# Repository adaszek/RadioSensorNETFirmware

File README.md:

# RF24 config required

Changes in RF24Network_config.h:

```
#define DISABLE_USER_PAYLOADS
#define ENABLE_SLEEP_MODE
```

Changes in RF24Mech_config.h:
```
#define MESH_NOMASTER
```

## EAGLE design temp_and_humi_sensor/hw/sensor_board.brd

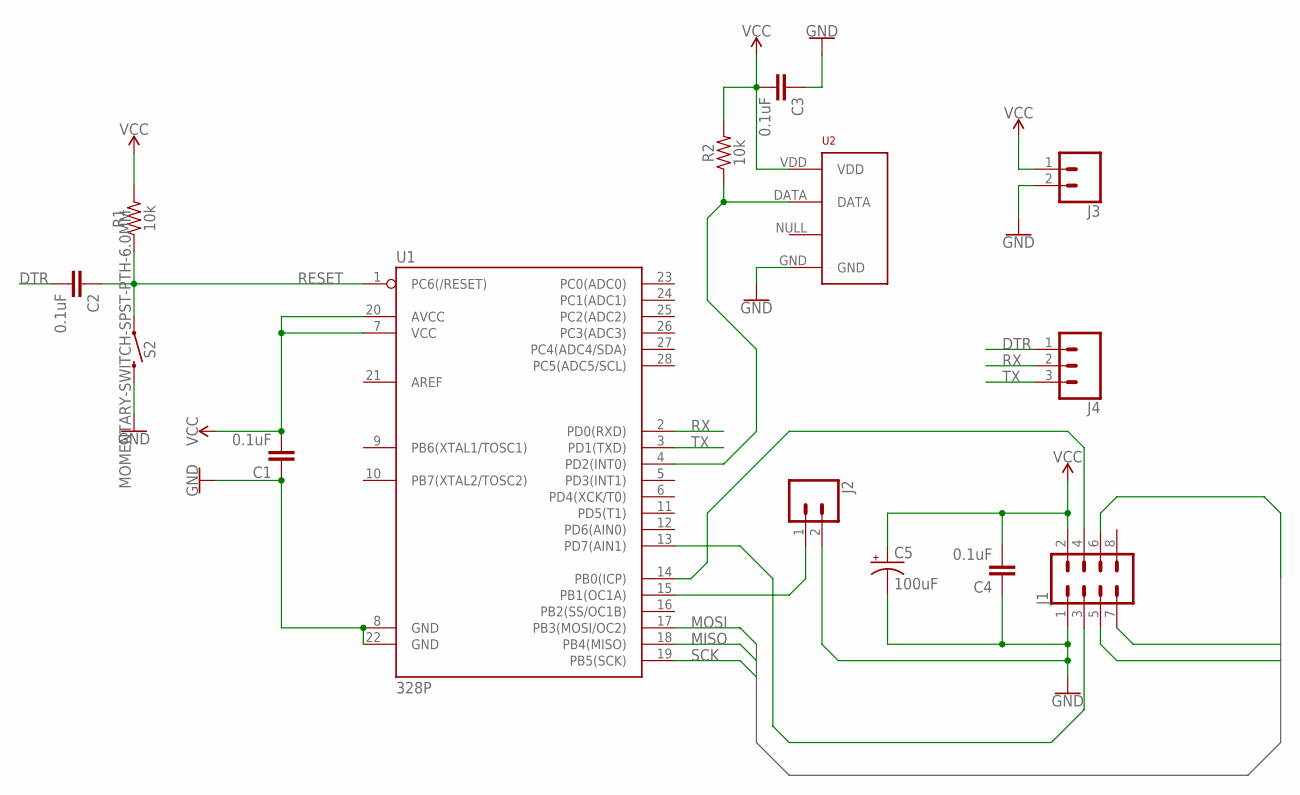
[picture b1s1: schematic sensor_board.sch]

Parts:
C1, C2, C3, C4: 0.1uF; CAP-PTH-SMALL-KIT
C5: 100uF; CPOL-RADIAL-2.5MM-6.5MM
J1: CONN_04X2; 2X4
J2, J3: CONN_02; 1X02
J4: CONN_03; 1X03
R1, R2: 10k; AXIAL-0.3
S2: MOMENTARY-SWITCH-SPST-PTH-6.0MM; TACTILE_SWITCH_PTH_6.0MM
U1: 328P; DIP28
U2: RHT03_DHT-22_AM2302RA; RHT03_DHT-22/RA

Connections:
DTR: C2.2, J4.1
GND: C1.1, C3.1, C4.1, C5.2 (-), J1.1, J2.2, J3.2, S2.3 (2), U1.8 (GND), U1.22 (GND), U2.GND
MISO: J1.7, U1.18 (PB4(MISO))
MOSI: J1.6, U1.17 (PB3(MOSI/OC2))
unnamed: J2.1, U1.15 (PB1(OC1A))
unnamed: J1.3, U1.13 (PD7(AIN1))
unnamed: J1.4, U1.14 (PB0(ICP))
unnamed: R2.P$1 (1), U1.4 (PD2(INT0)), U2.DATA
RESET: C2.1, R1.P$1 (1), S2.1, U1.1 (PC6(/RESET))
RX: J4.2, U1.2 (PD0(RXD))
SCK: J1.5, U1.19 (PB5(SCK))
TX: J4.3, U1.3 (PD1(TXD))
VCC: C1.2, C3.2, C4.2, C5.1 (+), J1.2, J3.1, R1.P$2 (2), R2.P$2 (2), U1.7 (VCC), U1.20 (AVCC), U2.VDD

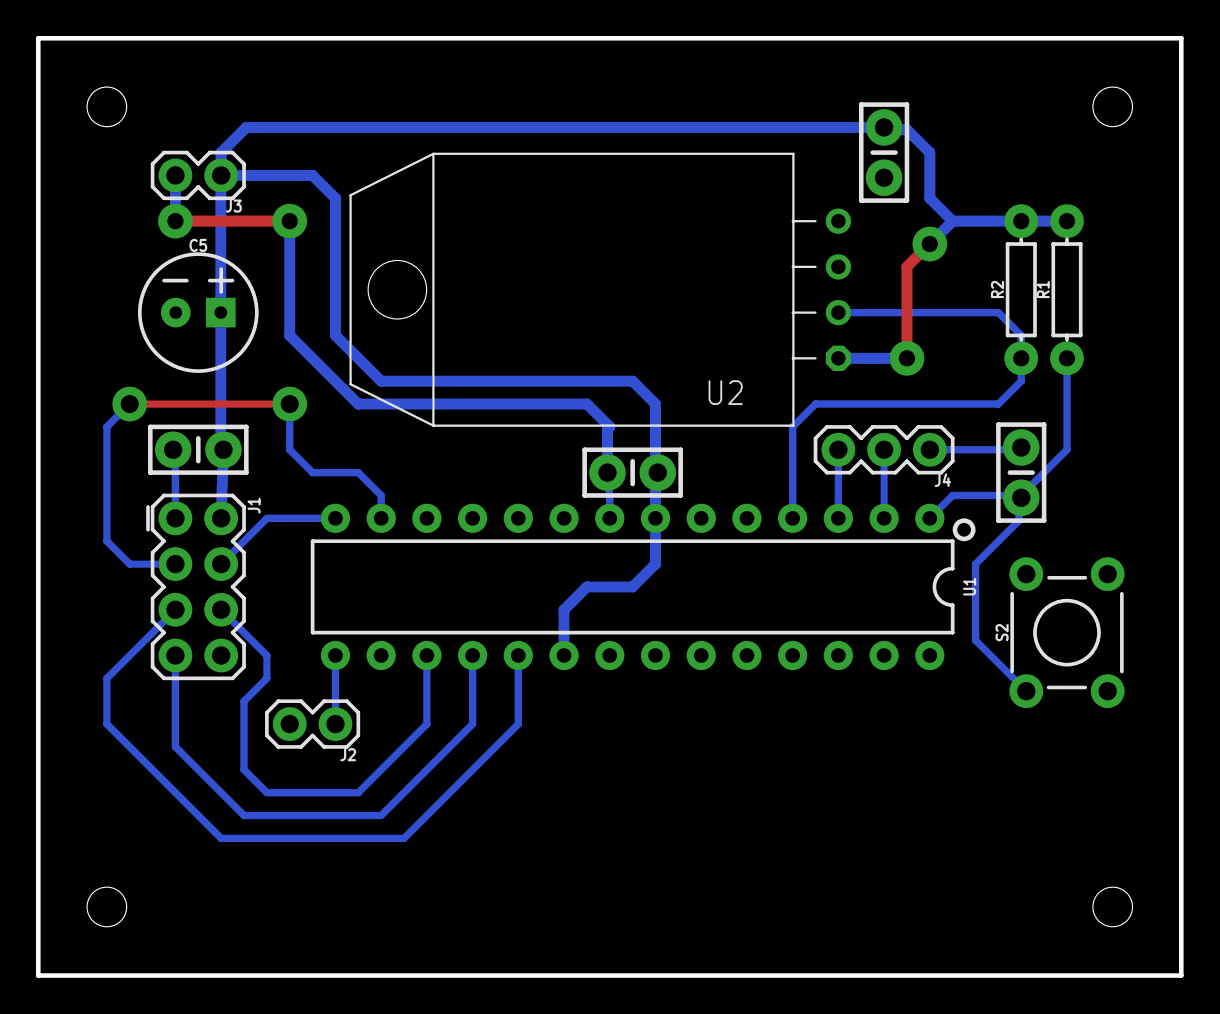
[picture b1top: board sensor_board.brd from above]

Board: 2 copper layers, 63.5 x 52.1 mm, 14 parts (0 on the bottom side), 13 nets.

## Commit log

2017-01-21 Renamed directory to fit convention.
2017-01-28 Added support for string publish, sensor publish on startup
2017-01-28 Reduced delay to the first publish
2017-02-19 Sensors report itselfs as new sensor after id change + fixed bug in app.js
2017-02-19 Sensors publishes its functions during connection
2017-02-22 Added history of startups in redis. Sensors publish also information about sleep time.
2017-04-09 Started with datetime picker and changed config pin in firmware
2017-04-12 Clean up of definition usage
2017-04-17 Added TODO to fix possible problem in sensor reconnection
2017-04-21 Moved handling of mesh into mqtt_abstraction
2017-04-23 Changed places where radio is powered
2017-04-30 Added basic test environment
2017-05-20 Removed unnecessary update()
2017-05-20 Removed tests
2017-05-20 Changed directory structure and added initial hw design
2017-05-20 Fixed power lines
2017-05-20 Added bigger capacitor
2017-08-20 Updated toolchain to gcc 5.4.0 + enabled -flto
2017-12-03 Changed gcc to 7.2
2017-12-03 Quick and dirty change of mqtt library
2017-12-04 Clean up

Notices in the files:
parts and their libraries:
SparkFun-Connectors: Licensing: Creative Commons ShareAlike 4.0 International - https://creativecommons.org/licenses/by-sa/4.0
